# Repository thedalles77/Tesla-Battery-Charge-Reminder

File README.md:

# Tesla-Battery-Charge-Reminder
Arduino Nano or ATTiny85 sounds a buzzer if the Tesla is in the garage but not plugged in.

This project is described in the Arduino Project Hub site:

https://create.arduino.cc/projecthub/thedalles77/tesla-battery-charge-reminder-347bca?ref=search&ref_id=tesla%20battery%20charge%20reminder&offset=0

Read the PDF "Tesla Charge Reminder" for more details.

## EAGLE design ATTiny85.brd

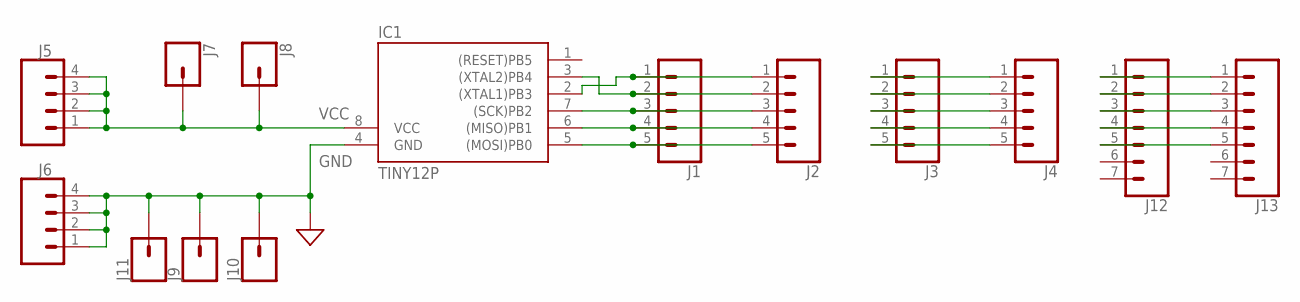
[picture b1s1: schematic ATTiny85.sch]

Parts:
IC1: TINY12P; DIL08
J1, J2, J3, J4: CONN_05NO_SILK; 1X05_NO_SILK
J5, J6: CONN_041X04_NO_SILK; 1X04_NO_SILK
J7, J8, J9, J10, J11: CONN_01PTH_NO_SILK_KIT; 1X01NS_KIT
J12, J13: CONN_07NO_SILK; 1X07_NO_SILK

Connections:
GND: IC1.4 (GND), J6.1, J6.2, J6.3, J6.4, J9.1, J10.1, J11.1
unnamed: J3.1, J4.1
unnamed: J3.2, J4.2
unnamed: IC1.2 ((XTAL1)PB3), J1.1, J2.1
unnamed: IC1.3 ((XTAL2)PB4), J1.2, J2.2
unnamed: IC1.7 ((SCK)PB2), J1.3, J2.3
unnamed: IC1.6 ((MISO)PB1), J1.4, J2.4
unnamed: IC1.5 ((MOSI)PB0), J1.5, J2.5
unnamed: J3.3, J4.3
unnamed: J3.4, J4.4
unnamed: J3.5, J4.5
unnamed: J12.1, J13.1
unnamed: J12.2, J13.2
unnamed: J12.3, J13.3
unnamed: J12.4, J13.4
unnamed: J12.5, J13.5
VCC: IC1.8 (VCC), J5.1, J5.2, J5.3, J5.4, J7.1, J8.1

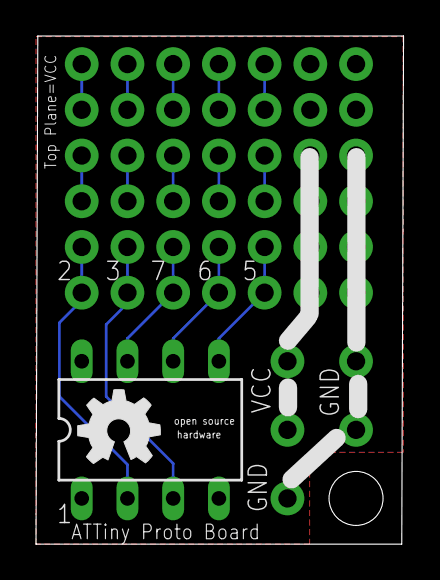
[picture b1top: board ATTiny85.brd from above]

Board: 2 copper layers, 20.4 x 28.2 mm, 15 parts (0 on the bottom side), 17 nets.

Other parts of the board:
U$1: OSHW_5MM

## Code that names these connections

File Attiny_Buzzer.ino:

/* Copyright 2021 Frank Adams
   Licensed under the Apache License, Version 2.0 (the "License");
   you may not use this file except in compliance with the License.
   You may obtain a copy of the License at
       http://www.apache.org/licenses/LICENSE-2.0
   Unless required by applicable law or agreed to in writing, software
   distributed under the License is distributed on an "AS IS" BASIS,
   WITHOUT WARRANTIES OR CONDITIONS OF ANY KIND, either express or implied.
   See the License for the specific language governing permissions and
   limitations under the License.
*/
// I refuse to pay $50 for a third party phone app to let me know I forgot to plug in my Tesla. Hopefully Tesla will add 
// this function to their phone app in the future but in the mean time, I've built a simple circuit based on an ATTiny85.  
// It will turn on a buzzer if the Tesla has been sitting in the garage for 30 minutes or more and the charge cables
// are still coiled on the wall hook. There is a push button switch at the base of the wall hook that is depressed by the 
// weight of the cables. The switch is monitored by the ATTiny. 
// The ATTiny controls an HC-SR04 ultrasonic sensor which is aimed at the Tesla that is about 3 feet away when in the garage. 
// If the Tesla is not in the garage, the HC-SR04 measures over 10 feet to the far wall. An LED is controlled by the ATTiny 
// that blinks 1 to 9 times to indicate a distance of 1 to 9 feet. Blink rate is 1 second. If the distance is 10 feet or more, 
// the LED blinks slowly at a rate of 5 seconds "on" & 5 seconds "off". The ATTiny repeats the loop every 10 seconds. 
// The circuit is powered by a 5 Volt 1 Amp wall wart supply.     
//
// Release History
// Dec 23, 2021  Original Release

// ATTiny Pins (Reset on pin 1 is not used and is internaly pulled up to 5 volts)
#define Trig 3 // PB3 = Pin 2; Logic output to the Trig pin of the HC-SR04. (10us high pulse to trigger)
#define Echo 4 // PB4 = Pin 3; Logic input from the Echo pin of the HC-SR04 (High pulse duration is round trip time)
#define Switch 0 // PB0 = Pin 5; Logic input from the pulled up push button switch in the charge cable wall hook (1=Open)
#define Buzzer 1 // PB1 = Pin 6; Logic output to turn on the active buzzer (thru an NPN transistor). (1=On)
#define LED 2 // PB2 = Pin 7; Logic output to turn on an LED (1=On)
// Globals
int feet; // Distance to car in feet
int last_feet = 3; // previous loop feet value
long roundtrip; // Trig signal pulse duration (over and back)
long time_count = 0; // counter
//
// Function reads the distance from the HC-SR04
int measure(void) 
{ 
  digitalWrite(Trig, HIGH); // Send HC-SR04 trigger signal high
  delayMicroseconds(10); // Hold the trigger signal high for 10 usec
  digitalWrite(Trig, LOW); // Send HC-SR04 trigger signal LOW
  int roundtrip = pulseIn(Echo, HIGH); // measure echo pin high pulse width
  return (roundtrip / 1776); // distance to car in feet
}
//
// Function to blink the LED based on the measured distance in feet. This function takes a total time of 10 seconds.
void blink_led(int feet)   
{
  if (feet < 1) { // Do not blink if under 1 foot
    digitalWrite(LED, LOW);
    delay(10000); // wait 10 seconds with the led off
  }
  else if (feet > 9) { // Give long single blink to indicate 10 or more feet
    digitalWrite(LED, HIGH);
    delay(5000); // 5 seconds turned on
    digitalWrite(LED, LOW);
    delay(5000); // 5 seconds turned off
  }
  else {  // the number of LED blinks equals the number of feet 
    for (int i=0; i<feet; i++) {
    digitalWrite(LED, HIGH); // turn on LED
    delay(500); // 1/2 second turned on
    digitalWrite(LED, LOW); // turn off LED
    delay(500); // 1/2 second turned off
    }
    delay(10000-(feet*1000)); // Delay 10 seconds - (feet) seconds
  }
}
//
void setup()
{
  pinMode(Echo, INPUT); // Define HC-SR04 Echo signal as an input
  pinMode(Switch, INPUT); // Define signal from push button switch as an input
  pinMode(Trig, OUTPUT); // Define trigger signal to HC-SR04 as an output
  pinMode(LED, OUTPUT); // Define LED signal as an output
  pinMode(Buzzer, OUTPUT); // Define buzzer signal as an output
  digitalWrite(Trig, LOW); // Send HC-SR04 trigger signal to the resting LOW state
  digitalWrite(LED, LOW); // turn off led
  time_count = 0; // initialize counter to zero
  // Sound Buzzer to confirm operation
  digitalWrite(Buzzer, HIGH); // turn on buzzer
  delay(1000); // wait 1 second 
  digitalWrite(Buzzer, LOW); // turn off buzzer
}
   
void loop() // This loop repeats every 10 seconds 
{
  feet = measure(); // measure the distance in feet to the car (or the far wall)
  if (!digitalRead(Switch) && (feet <= 7)) {  // check if not plugged in and car is in the garage
    time_count++; // increment the counter (a bad distance reading will increment the counter but get zero'ed on the next loop)
  }
  else if (digitalRead(Switch)) {
    time_count = 0; // zero the counter because the car is plugged in
  }
  else if ((last_feet >= 8) && (feet >= 8))  { 
    time_count = 0; // zero the counter  if 2 loops in a row show car is out of the garage (won't zero if 1 bad distance reading)
  }
//
  if (time_count >= 180) { // 180 loops equals 30 minutes
    digitalWrite(Buzzer, HIGH); // turn on buzzer
  }
  else {
    digitalWrite(Buzzer, LOW); // turn off buzzer
  }
//
  blink_led(feet); // blink the led to indicate the distance in feet. This takes 10 seconds.
//
  last_feet = feet; // save measurement for next loop in case of a bad/noisy read
//
}

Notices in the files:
parts and their libraries:
SparkFun-Connectors: Licensing: Creative Commons ShareAlike 4.0 International - https://creativecommons.org/licenses/by-sa/4.0
